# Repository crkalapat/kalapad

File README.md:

# Kalapad

_A custom QMK-based 9 key macropad_

## Features

- 9 programmable macro switches
- Cherry MX Switch compatibility
- SK6812-E RGB LED indicator light
- EC11 Rotary Encoder for volume control
- Matrix-style switch layout

## Demo

https://github.com/user-attachments/assets/4e5cf57b-7511-4118-89fe-79310d505cb6

## Design

### PCB

### Schematic

## BOM

- 9x Cherry MX Switches
- 1x SK6812-E LED
- 1x EC11 Rotary Encoder
- 1x Seeed Studio XIAO RP2040
- 3x M3x16mm screws
- 1x M3x4mm screw
- 1x 3D-Printed Case (Top and Bottom)
- 1x PCB

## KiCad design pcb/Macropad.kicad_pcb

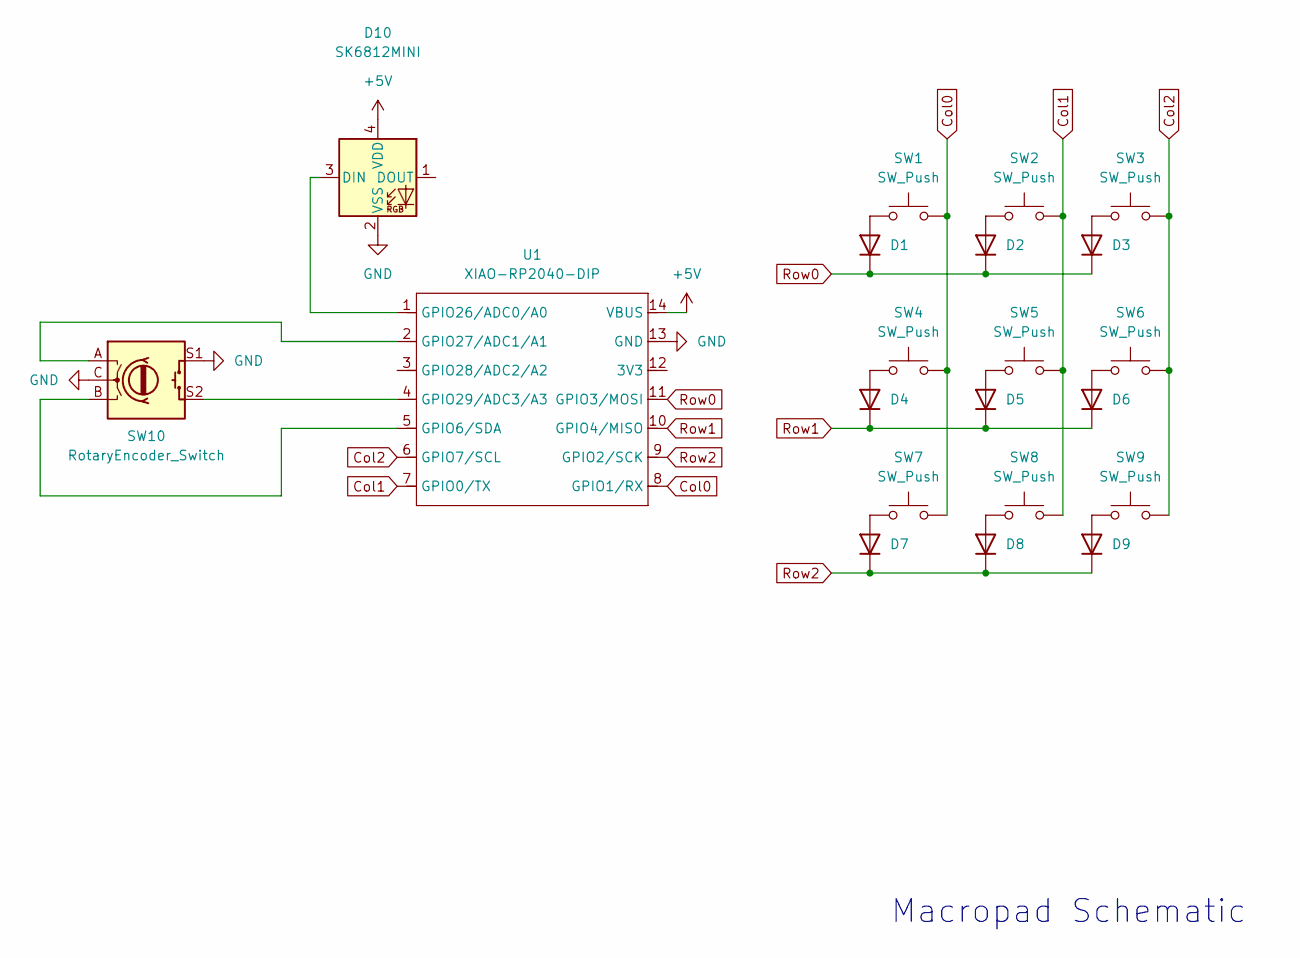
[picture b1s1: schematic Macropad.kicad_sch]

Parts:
D1, D2, D3, D4, D5, D6, D7, D8, D9: D_A-405_P5.08mm_Vertical_AnodeUp
D10: SK6812MINI; LED_SK6812MINI_PLCC4_3.5x3.5mm_P1.75mm
SW1, SW2, SW3, SW4, SW5, SW6, SW7, SW8, SW9: SW_Push; SW_Cherry_MX_1.00u_PCB
SW10: RotaryEncoder_Switch; RotaryEncoder_Alps_EC11E-Switch_Vertical_H20mm
U1: XIAO-RP2040-DIP

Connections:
+5V: D10.4 (VDD), U1.14 (VBUS)
Col0: SW1.2, SW4.2, SW7.2, U1.8 (GPIO1/RX)
Col1: SW2.2, SW5.2, SW8.2, U1.7 (GPIO0/TX)
Col2: SW3.2, SW6.2, SW9.2, U1.6 (GPIO7/SCL)
GND: D10.2 (VSS), SW10.C, SW10.S1, U1.13 (GND)
unnamed: D1.2 (A), SW1.1
unnamed: D2.2 (A), SW2.1
unnamed: D3.2 (A), SW3.1
unnamed: D4.2 (A), SW4.1
unnamed: D5.2 (A), SW5.1
unnamed: D6.2 (A), SW6.1
unnamed: D7.2 (A), SW7.1
unnamed: D8.2 (A), SW8.1
unnamed: D9.2 (A), SW9.1
unnamed: D10.3 (DIN), U1.1 (GPIO26/ADC0/A0)
unnamed: SW10.B, U1.5 (GPIO6/SDA)
unnamed: SW10.A, U1.2 (GPIO27/ADC1/A1)
unnamed: SW10.S2, U1.4 (GPIO29/ADC3/A3)
Row0: D1.1 (K), D2.1 (K), D3.1 (K), U1.11 (GPIO3/MOSI)
Row1: D4.1 (K), D5.1 (K), D6.1 (K), U1.10 (GPIO4/MISO)
Row2: D7.1 (K), D8.1 (K), D9.1 (K), U1.9 (GPIO2/SCK)

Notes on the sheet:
Macropad Schematic

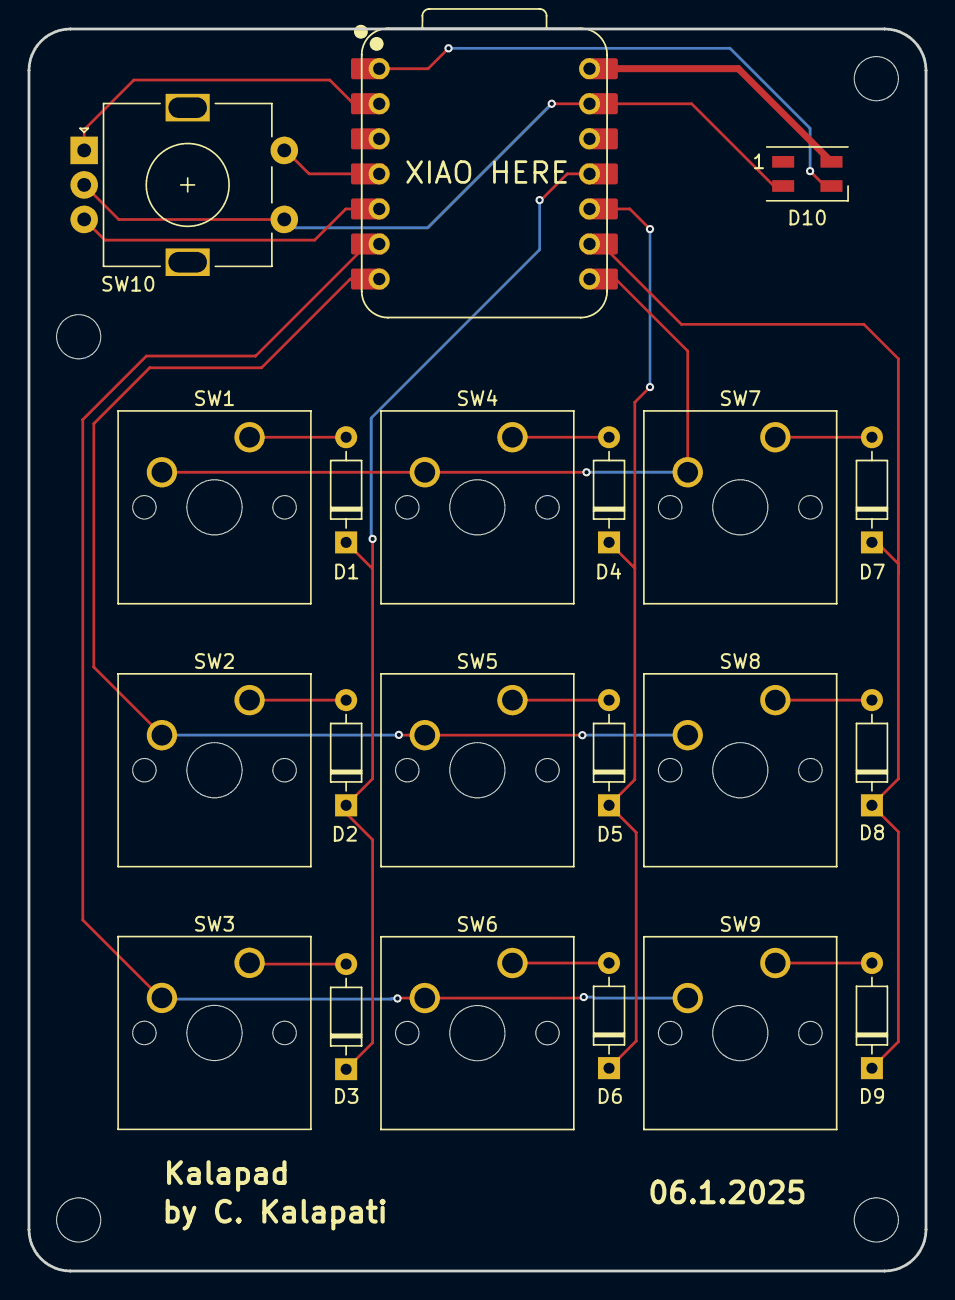
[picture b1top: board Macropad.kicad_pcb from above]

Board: 2 copper layers, 65.0 x 90.0 mm, 21 parts (0 on the bottom side), 21 nets.

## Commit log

2025-06-09 Add images, case CAD files, README
2025-06-09 Add assembly image to README
2025-06-10 Add firmware, update README
2025-06-10 Modify README
2025-06-10 Fix BOM
2025-06-10 Add firmware files
2025-06-10 Add uf2 to firmware directory:
2025-06-10 Add PCB files
2025-06-10 Add assembly CAD, change README
2025-07-01 Add fillet edge
2026-06-22 Add demo video to README
2026-06-22 Add gitignore and assembled picture
